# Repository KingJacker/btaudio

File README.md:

# btaudio — Audiophiles Bluetooth 5.1 Upgrade-Board für Kopfhörer

Ein kompromissloses Wireless-Upgrade-Modul für Kabelkopfhörer. Kein All-in-One-Kompromiss — stattdessen drei dedizierte Stufen für maximale Klangqualität ohne Hintergrundrauschen.

## Architektur

```
QCC5125 (BT 5.1)  →[I2S]→  PCM5102A (DAC)  →[Analog]→  TPA6132A2 (Amp)  →  Kopfhörer
   Empfang                    Wandlung                     Verstärkung
```

**Stufe 1 — Empfang:** QCC5125 empfängt High-Res-Audio via aptX HD / LDAC und gibt das Signal rein digital (I2S) weiter. Keine Funkstörungen im Analogpfad.

**Stufe 2 — Wandlung:** PCM5102A (High-End-DAC) wandelt das I2S-Signal in ein sauberes analoges Audiosignal. Dedizierter Chip statt integriertem DAC-Billigst-Lösung.

**Stufe 3 — Verstärkung:** TPA6132A2 treibt die Kopfhörer direkt an ("Capless"-Design) — keine Elektrolytkondensatoren im Signalweg, die den Klang verfärben.

## Schaltplan

## Platine (3D-Ansicht)

## Ziel

Alte, hochwertige Kabelkopfhörer auf modernes audiophiles Bluetooth-Niveau heben — durch konsequente Trennung von Funk, DA-Wandlung und Verstärkung.

## Hardware

- **BT-Modul:** Qualcomm QCC5125 (Bluetooth 5.1, aptX HD, LDAC)
- **DAC:** Texas Instruments PCM5102A
- **Amp:** Texas Instruments TPA6132A2 (Capless Headphone Amp)
- **Design-Tool:** KiCad

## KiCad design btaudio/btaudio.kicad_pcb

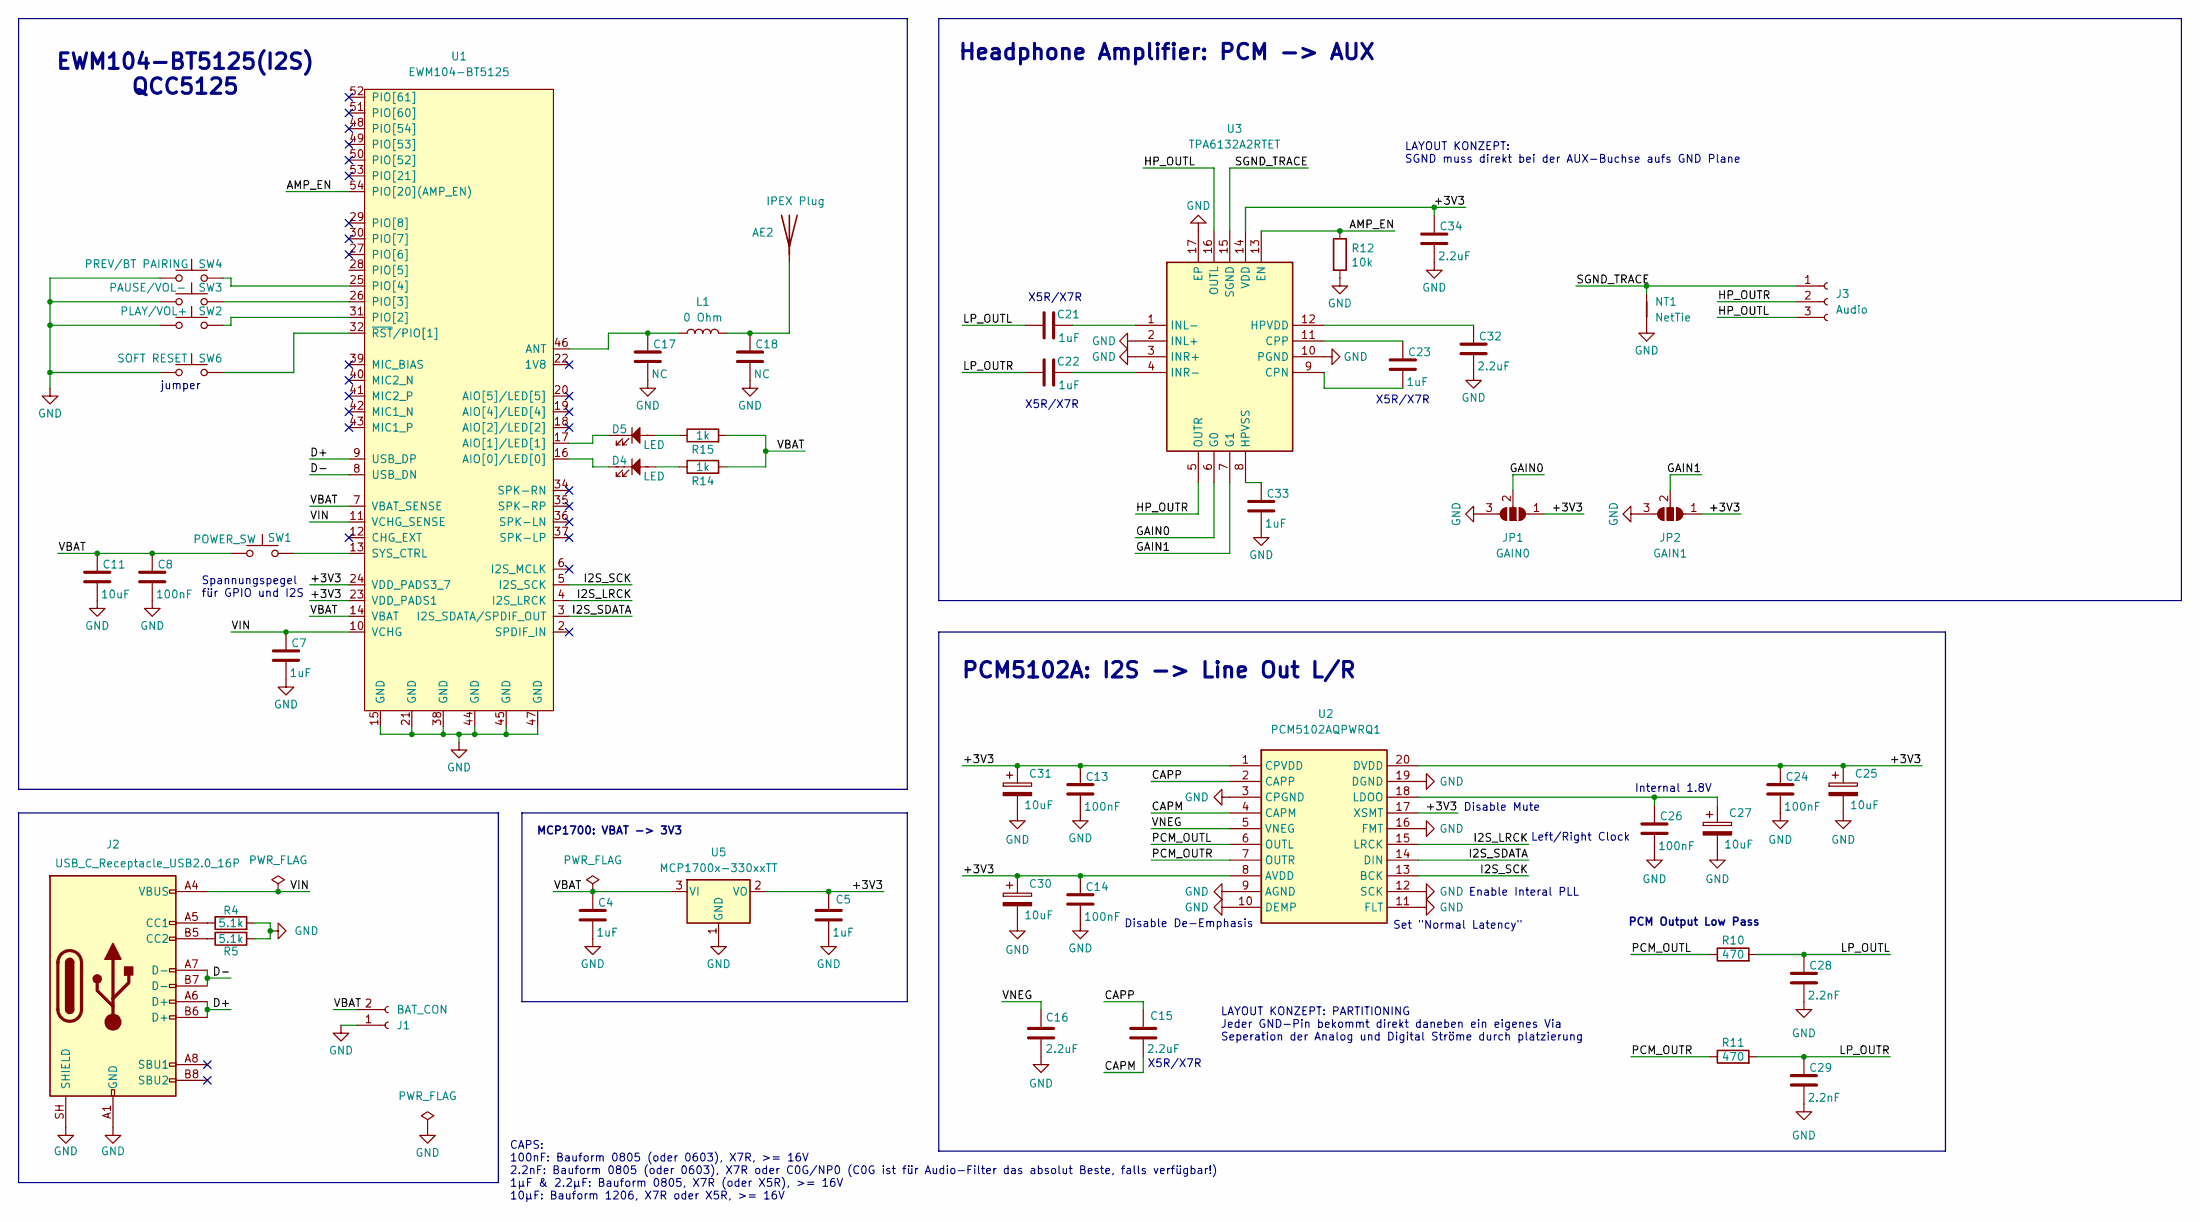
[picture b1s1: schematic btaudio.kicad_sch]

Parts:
AE2: IPEX Plug; A1JB
C4, C5, C7, C21, C22, C23, C33: 1uF; C_0805_2012Metric
C8, C13, C14, C24, C26: 100nF; C_0805_2012Metric
C11, C25, C27, C30, C31: 10uF; C_1206_3216Metric
C15, C16, C32, C34: 2.2uF; C_0805_2012Metric
C17, C18: NC; C_0402_1005Metric
C28, C29: 2.2nF; C_0805_2012Metric
D4, D5: LED; LED_0805_2012Metric
J1: BAT_CON; JST_SH_SM02B-SRSS-TB_1x02-1MP_P1.00mm_Horizontal
J2: USB_C_Receptacle_USB2.0_16P; USB_C_Receptacle_HRO_TYPE-C-31-M-12
J3: Audio; Resonator_SMD-3Pin_7.2x3.0mm_BigPads
JP1: GAIN0; SolderJumper-3_P1.3mm_Open_RoundedPad1.0x1.5mm
JP2: GAIN1; SolderJumper-3_P1.3mm_Open_RoundedPad1.0x1.5mm
L1: 0 Ohm; L_0402_1005Metric
NT1: NetTie; NetTie-2_SMD_Pad0.5mm
R4, R5: 5.1k; R_0805_2012Metric
R10, R11: 470; R_0805_2012Metric
R12: 10k; R_0805_2012Metric
R14, R15: 1k; R_0805_2012Metric
SW1: POWER_SW; SW_SPST_TS-1088-xR020
SW2: PLAY/VOL+; SW_SPST_TS-1088-xR020
SW3: PAUSE/VOL-; SW_SPST_TS-1088-xR020
SW4: PREV/BT PAIRING; SW_SPST_TS-1088-xR020
SW6: SOFT RESET; SolderJumper-2_P1.3mm_Open_RoundedPad1.0x1.5mm
U1: EWM104-BT5125; EWM104-BT5125(KiCAD)
U2: PCM5102AQPWRQ1; SOP65P640X120-20N
U3: TPA6132A2RTET; QFN50P300X300X80-17N-D
U5: MCP1700x-330xxTT; SOT-23

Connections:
/+3V3: C5.1, C13.1, C14.1, C24.1, C25.1, C30.1, C31.1, C34.1, JP1.1 (A), JP2.1 (A), U1.23 (VDD_PADS1), U1.24 (VDD_PADS3_7), U2.1 (CPVDD), U2.8 (AVDD), U2.17 (XSMT), U2.20 (DVDD), U3.14 (VDD), U5.2 (VO)
/AMP_EN: R12.1, U1.54 (PIO[20](AMP_EN)), U3.13 (EN)
/CAPM: C15.2, U2.4 (CAPM)
/CAPP: C15.1, U2.2 (CAPP)
/D+: J2.A6 (D+), J2.B6 (D+), U1.9 (USB_DP)
/D-: J2.A7 (D-), J2.B7 (D-), U1.8 (USB_DN)
/GAIN0: JP1.2 (C), U3.6 (G0)
/GAIN1: JP2.2 (C), U3.7 (G1)
/HP_OUTL: J3.3, U3.16 (OUTL)
/HP_OUTR: J3.2, U3.5 (OUTR)
/I2S_LRCK: U1.4 (I2S_LRCK), U2.15 (LRCK)
/I2S_SCK: U1.5 (I2S_SCK), U2.13 (BCK)
/I2S_SDATA: U1.3 (I2S_SDATA/SPDIF_OUT), U2.14 (DIN)
/LP_OUTL: C21.1, C28.1, R10.2
/LP_OUTR: C22.1, C29.1, R11.2
/PCM_OUTL: R10.1, U2.6 (OUTL)
/PCM_OUTR: R11.1, U2.7 (OUTR)
/SGND_TRACE: J3.1, NT1.2, U3.15 (SGND)
/VIN: C7.1, J2.A4 (VBUS), J2.A9 (VBUS), J2.B4 (VBUS), J2.B9 (VBUS), U1.10 (VCHG), U1.11 (VCHG_SENSE)
/VNEG: C16.2, U2.5 (VNEG)
GND: C4.2, C5.2, C7.2, C8.2, C11.2, C13.2, C14.2, C16.1, C17.2, C18.2, C24.2, C25.2, C26.2, C27.2, C28.2, C29.2, C30.2, C31.2, C32.2, C33.2, C34.2, J1.1, J2.A1 (GND), J2.A12 (GND), J2.B1 (GND), J2.B12 (GND), J2.SH (SHIELD), JP1.3 (B), JP2.3 (B), NT1.1, R4.2, R5.2, R12.2, SW2.1, SW3.1, SW4.1, SW6.1, U1.15 (GND), U1.21 (GND), U1.38 (GND), U1.44 (GND), U1.45 (GND), U1.47 (GND), U2.3 (CPGND), U2.9 (AGND), U2.10 (DEMP), U2.11 (FLT), U2.12 (SCK), U2.16 (FMT), U2.19 (DGND), U3.2 (INL+), U3.3 (INR+), U3.10 (PGND), U3.17 (EP), U5.1 (GND); also elsewhere on the board
unnamed: AE2.1 (A_1), C18.1, L1.2
unnamed: D4.2, R14.1
unnamed: D5.2, R15.1
unnamed: J1.3, SW3.2, U1.26 (PIO[3])
unnamed: J1.4, SW4.2, U1.25 (PIO[4])
unnamed: J2.A5 (CC1), R4.1
unnamed: J2.B5 (CC2), R5.1
unnamed: D4.1, U1.16 (AIO[0]/LED[0])
unnamed: D5.1, U1.17 (AIO[1]/LED[1])
unnamed: C17.1, L1.1, U1.46 (ANT)
unnamed: SW1.2, U1.13 (SYS_CTRL)
unnamed: SW6.2, U1.32 (~RST/PIO[1])
unnamed: C26.1, C27.1, U2.18 (LDOO)
unnamed: C23.2, U3.9 (CPN)
unnamed: C23.1, U3.11 (CPP)
unnamed: C32.1, U3.12 (HPVDD)
unnamed: C33.1, U3.8 (HPVSS)
unnamed: C21.2, U3.1 (INL-)
unnamed: C22.2, U3.4 (INR-)

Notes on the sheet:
Left/Right Clock
Spannungspegel für GPIO und I2S
PCM Output Low Pass
LAYOUT KONZEPT: PARTITIONING Jeder GND-Pin bekommt direkt daneben ein eigenes Via Seperation der Analog und Digital Ströme durch platzierung
Disable Mute
X5R/X7R
Set "Normal Latency"
MCP1700: VBAT -> 3V3
CAPS: 100nF: Bauform 0805 (oder 0603), X7R, >= 16V 2.2nF: Bauform 0805 (oder 0603), X7R oder C0G/NP0 (C0G ist für Audio-Filter das absolut Beste, falls verfügbar!) 1μF & 2.2μF: Bauform 0805, X7R (oder X5R), >= 16V 10μF: Bauform 1206, X7R oder X5R, >= 16V
jumper
Internal 1.8V
Disable De-Emphasis
LAYOUT KONZEPT: SGND muss direkt bei der AUX-Buchse aufs GND Plane
PCM5102A: I2S -> Line Out L/R
Enable Interal PLL
Headphone Amplifier: PCM -> AUX
EWM104-BT5125(I2S) QCC5125

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
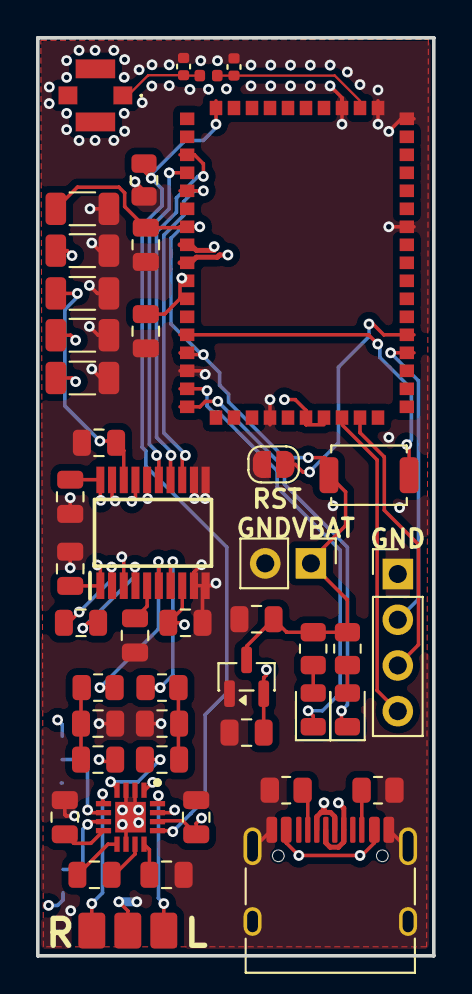
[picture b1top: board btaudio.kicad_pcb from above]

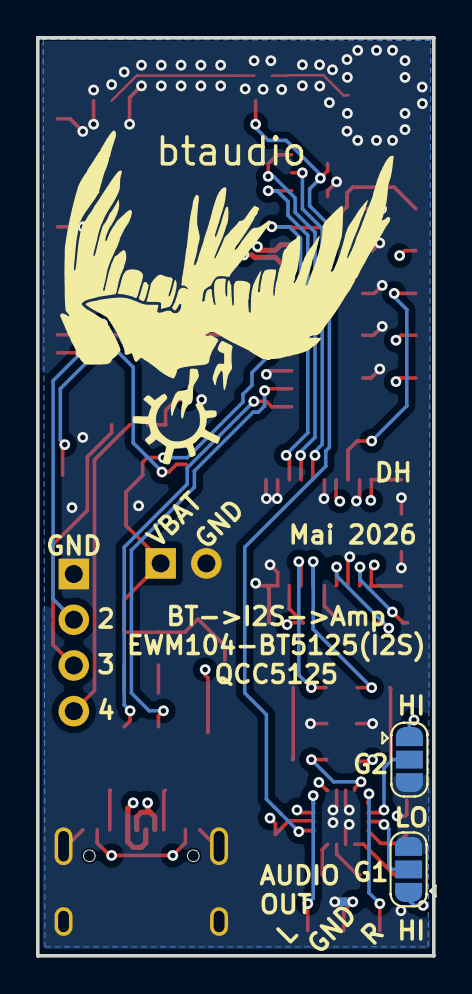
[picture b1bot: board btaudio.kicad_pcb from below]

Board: 4 copper layers, 22.0 x 51.0 mm, 49 parts (3 on the bottom side), 42 nets.

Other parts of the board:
J6: Battery; PinHeader_1x02_P2.54mm_Vertical

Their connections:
GND: J6.2; also elsewhere on the board

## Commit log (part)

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2026-05-06 first
2026-05-07 symbol
2026-05-07 some progress schema
2026-05-09 PCM5102A Schema done
2026-05-09 TPA6132A schema done
2026-05-11 schema done
2026-05-11 footprints assigned, img added
2026-05-11 readme
2026-05-11 bom & fix footprint
2026-05-14 removed lock file
2026-05-14 started on layout
2026-05-14 compacting layout
2026-05-18 primary layout done
2026-05-18 layout almost done v1
2026-05-19 wiring done
2026-05-19 fixed 3d models
2026-05-19 finished layout & aesthetics
2026-05-20 bom, img, prod files
